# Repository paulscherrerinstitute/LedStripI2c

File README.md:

# Bar-Graph Display Project

Display current pulse-ID on a LED-bar.
The LEDs are driven by PCA9955 LED controllers
and remote-controlled by I2C over a fiber
connection.

 - [kicad/](kicad/)

   Kicad design files; [schematics](kicad/ledstrip-sch.pdf) and pcb.

 - [hdl/](hdl/)

   vhdl code for driving the device from a FPGA
   ([documentation](hdl/README.md)).

 - [python/](python/)

   python scripts to drive the device from the USB/I2C
   adapter (for testing).

 - [PulseidExtractor/](PulseidExtractor/)

   submodule required to extract the pulse-id from an EVR320
   stream.

The LED device's I2C bus is accessible by three methods:

 - optical (light <-> logic 'low' on I2C bus) 
 - PMOD connector (1.5-3.3 V via i2c-transceiver) for
   connection, e.g., to a Zynq board.
 - USB-I2c bridge from host.

Note that in all use-cases power (5V, 350mA max.) must be
provided at the USB port (from host or USB wall-wart).

A mini-USB connector was deemed mechanically more stable than
micro-USB. USB-C would be an alternative.

Till Straumann, 10/2020.

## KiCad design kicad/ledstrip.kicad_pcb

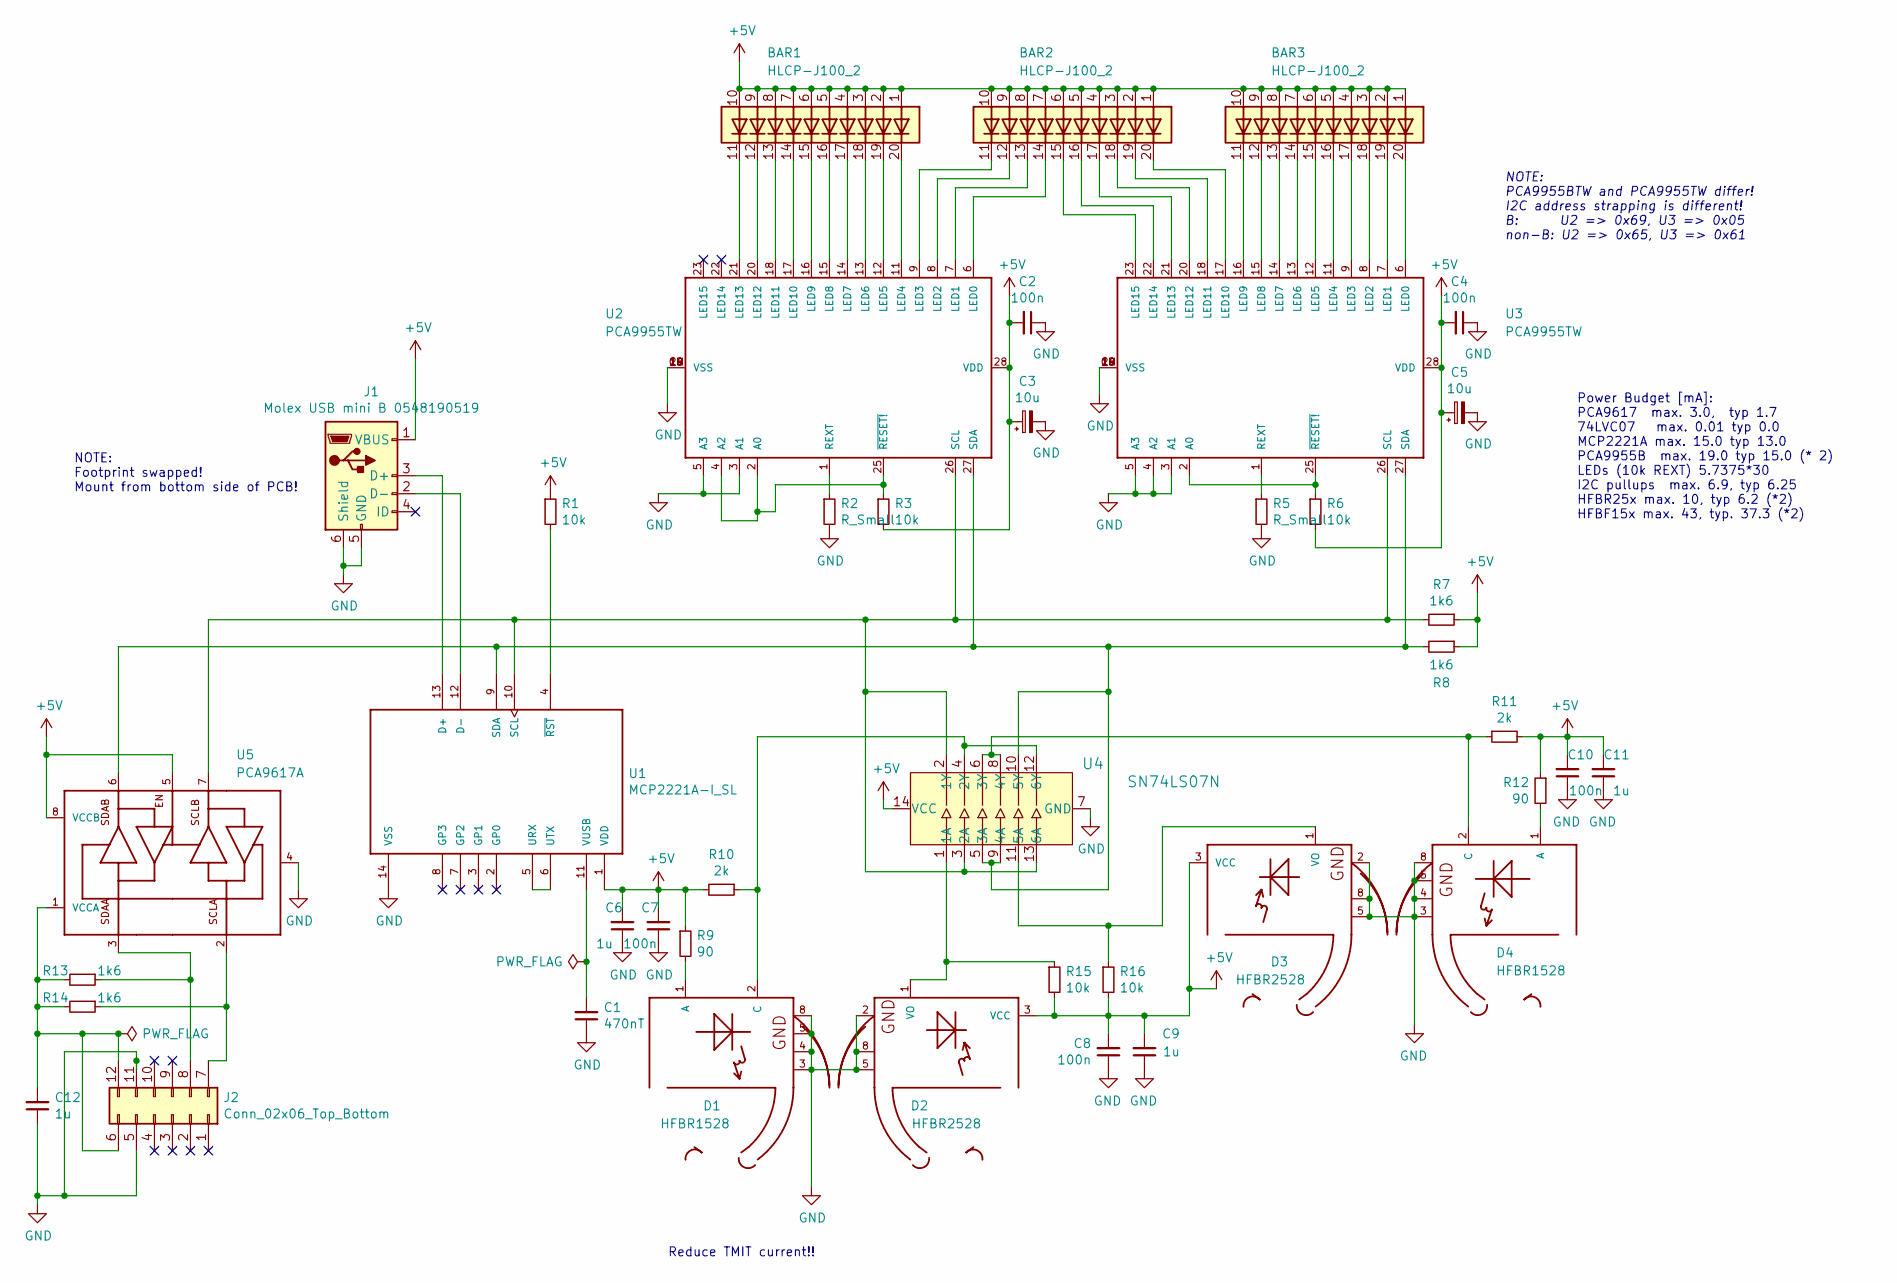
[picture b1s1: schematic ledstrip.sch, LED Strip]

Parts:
BAR1, BAR2, BAR3: HLCP-J100_2; HLCP-J100
C1: 470nT; C_0805_2012Metric
C2, C4, C7, C8, C10: 100n; C_0603_1608Metric
C3, C5: 10u; CP_EIA-3216-10_Kemet-I
C6, C9, C11, C12: 1u; C_0805_2012Metric
D1, D4: HFBR1528; HFBR25XX
D2, D3: HFBR2528; HFBR25XX
J1: Molex USB mini B 0548190519; USB_Mini_B_Female_548190519
J2: Conn_02x06_Top_Bottom; PMOD_PinHeader_2x06_P2.54mm_Horizontal
R1, R3, R6, R15, R16: 10k; R_0603_1608Metric
R2, R5: R_Small; R_0603_1608Metric
R7, R8, R13, R14: 1k6; R_0603_1608Metric
R9, R12: 90; R_1206_3216Metric
R10, R11: 2k; R_0603_1608Metric
U1: MCP2221A-I_SL; SOIC127P600X175-14N
U2, U3: PCA9955TW; SOT1172-2
U4: SN74LS07N; SOIC-14_3.9x8.7mm_P1.27mm; MPN SN74LS07N; Digi-Key_PN 296-1629-5-ND
U5: PCA9617A; TSSOP-8_W3mm

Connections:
+5V: BAR1.1 (A), BAR1.2 (A), BAR1.3 (A), BAR1.4 (A), BAR1.5 (A), BAR1.6 (A), BAR1.7 (A), BAR1.8 (A), BAR1.9 (A), BAR1.10 (A), BAR2.1 (A), BAR2.2 (A), BAR2.3 (A), BAR2.4 (A), BAR2.5 (A), BAR2.6 (A), BAR2.7 (A), BAR2.8 (A), BAR2.9 (A), BAR2.10 (A), BAR3.1 (A), BAR3.2 (A), BAR3.3 (A), BAR3.4 (A), BAR3.5 (A), BAR3.6 (A), BAR3.7 (A), BAR3.8 (A), BAR3.9 (A), BAR3.10 (A), C2.2, C3.1, C4.2, C5.1, C6.2, C7.2, C8.2, C9.2, C10.2, C11.2, D2.3 (VCC), D3.3 (VCC), J1.1 (VBUS), R1.1, R3.2, R6.2, R7.1, R8.1, R9.1, R10.2, R11.2, R12.1, R15.2, R16.2, U1.1 (VDD), U2.28 (VDD), U3.28 (VDD), U4.14 (VCC), U5.5, U5.8 (VCCB)
GND: C1.1, C2.1, C3.2, C4.1, C5.2, C6.1, C7.1, C8.1, C9.1, C10.1, C11.1, C12.1, D1.3, D1.4, D1.5, D1.8, D2.2, D2.5, D2.8, D3.2, D3.5, D3.8, D4.3, D4.4, D4.5, D4.8, J1.5 (GND), J1.6 (Shield), J2.5, J2.11, R2.2, R5.2, U1.14 (VSS), U2.3 (A1), U2.5 (A3), U2.10 (VSS), U2.19 (VSS), U2.24 (VSS), U2.CM (VSS), U3.3 (A1), U3.4 (A2), U3.5 (A3), U3.10 (VSS), U3.19 (VSS), U3.24 (VSS), U3.CM (VSS), U4.7 (GND), U5.4
unnamed: BAR1.11 (K), U2.21 (LED13)
unnamed: BAR1.12 (K), U2.20 (LED12)
unnamed: BAR1.13 (K), U2.18 (LED11)
unnamed: BAR1.14 (K), U2.17 (LED10)
unnamed: BAR1.15 (K), U2.16 (LED9)
unnamed: BAR1.16 (K), U2.15 (LED8)
unnamed: BAR1.17 (K), U2.14 (LED7)
unnamed: BAR1.18 (K), U2.13 (LED6)
unnamed: BAR1.19 (K), U2.12 (LED5)
unnamed: BAR1.20 (K), U2.11 (LED4)
unnamed: BAR2.11 (K), U2.9 (LED3)
unnamed: BAR2.12 (K), U2.8 (LED2)
unnamed: BAR2.13 (K), U2.7 (LED1)
unnamed: BAR2.14 (K), U2.6 (LED0)
unnamed: BAR2.15 (K), U3.23 (LED15)
unnamed: BAR2.16 (K), U3.22 (LED14)
unnamed: BAR2.17 (K), U3.21 (LED13)
unnamed: BAR2.18 (K), U3.20 (LED12)
unnamed: BAR2.19 (K), U3.18 (LED11)
unnamed: BAR2.20 (K), U3.17 (LED10)
unnamed: BAR3.11 (K), U3.16 (LED9)
unnamed: BAR3.12 (K), U3.15 (LED8)
unnamed: BAR3.13 (K), U3.14 (LED7)
unnamed: BAR3.14 (K), U3.13 (LED6)
unnamed: BAR3.15 (K), U3.12 (LED5)
unnamed: BAR3.16 (K), U3.11 (LED4)
unnamed: BAR3.17 (K), U3.9 (LED3)
unnamed: BAR3.18 (K), U3.8 (LED2)
unnamed: BAR3.19 (K), U3.7 (LED1)
unnamed: BAR3.20 (K), U3.6 (LED0)
unnamed: C1.2, U1.11 (VUSB)
unnamed: C12.2, J2.6, J2.12, R13.2, R14.2, U5.1 (VCCA)
unnamed: D1.1 (A), R9.2
unnamed: D1.2 (C), R10.1, U4.4 (2Y), U4.12 (6Y)
unnamed: D2.1 (VO), R15.1, U4.1 (1A)
unnamed: D3.1 (VO), R16.1, U4.11 (5A)
unnamed: D4.1 (A), R12.2
unnamed: D4.2 (C), R11.1, U4.6 (3Y), U4.8 (4Y)
unnamed: J1.2 (D-), U1.12 (D-)
unnamed: J1.3 (D+), U1.13 (D+)
unnamed: J2.7, R14.1, U5.2
unnamed: J2.8, R13.1, U5.3
unnamed: R1.2, U1.4 (~RST~)
unnamed: R2.1, U2.1 (REXT)
unnamed: R3.1, U2.2 (A0), U2.4 (A2), U2.25 (~RESET!~)
unnamed: R5.1, U3.1 (REXT)
unnamed: R6.1, U3.2 (A0), U3.25 (~RESET!~)
unnamed: R7.2, U1.10 (SCL), U2.26 (SCL), U3.26 (SCL), U4.2 (1Y), U4.3 (2A), U4.13 (6A), U5.7
unnamed: R8.2, U1.9 (SDA), U2.27 (SDA), U3.27 (SDA), U4.5 (3A), U4.9 (4A), U4.10 (5Y), U5.6
unnamed: U1.5 (URX), U1.6 (UTX)

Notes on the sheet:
Reduce TMIT current!!
Power Budget [mA]: PCA9617 max. 3.0, typ 1.7 74LVC07 max. 0.01 typ 0.0 MCP2221A max. 15.0 typ 13.0 PCA9955B max. 19.0 typ 15.0 (* 2) LEDs (10k REXT) 5.7375*30 I2C pullups max. 6.9, typ 6.25 HFBR25x max. 10, typ 6.2 (*2) HFBF15x max. 43, typ. 37.3 (*2)
NOTE: PCA9955BTW and PCA9955TW differ! I2C address strapping is different! B: U2 => 0x69, U3 => 0x05 non-B: U2 => 0x65, U3 => 0x61
NOTE: Footprint swapped! Mount from bottom side of PCB!

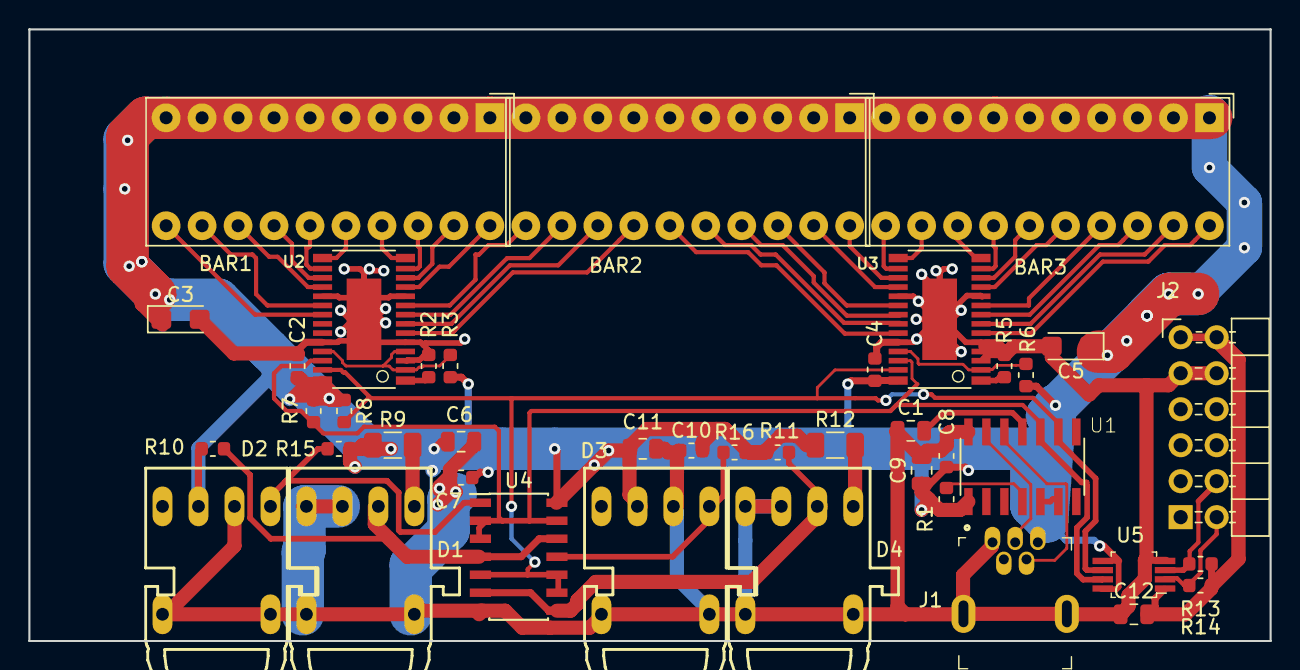
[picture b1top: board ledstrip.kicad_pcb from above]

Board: 2 copper layers, 87.6 x 43.2 mm, 41 parts (0 on the bottom side), 52 nets.

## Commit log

2020-10-08 Added new...
2020-10-08 First python implementation
2020-10-08 mcp2221_i2c.py: added more functionality
2020-10-08 renamed mcp2221_i2c.py -> Mcp2221I2c,py; added LedStrip.py
2020-10-08 changed some sleep times in test routine
2020-10-08 LedStrip.py: setPwmIref() accepts arrays/collections
2020-10-14 Mcp2221I2c.py: Support writing chip settings to flash
2020-10-15 Changed 'drain'; support restart+write; ensure device is drained before sending new read/write commands
2020-10-20 initial import from PON
2020-10-20 ioxos_mpc_master_i2c_ctl.vhd: convert to numeric_std; don't set ila signals if ila is disabled
    setting ila signals caused warnings about to_unsigned range errors
    (target slv too short).
2020-10-20 ila_dummy.vhd: added (for ghdl)
2020-10-20 i2ctb.vhd: added test bed
2020-10-20 i2ctb.vhd: added several helper procedures
2020-10-21 Added PulseID Extractor module.
    Extract pulse ID from EVR stream.
2020-10-21 Added MpcI2cSequencer
2020-10-21 made initial FDR value a generic
2020-10-21 Added LedStripController.vhd
2020-10-21 - added i2cRegSlaveWrap.vhd for testing
2020-10-21 ioxos_mpc_master_i2c_ctl.vhd: support small prescaler dividers
    If FDR(7) is set then we use FDR(6 downto 0) literally.
    Also: allow for read-only FDR (save a bit of logic) via generic
2020-10-21 bugfixes
2020-10-21 Added LedStripMmioWrapper.vhd
2020-10-21 Moved test code to 'tb/'
2020-10-21 more test code to 'tb/'
2020-10-21 made strobe rate run-time modifiable
2020-10-21 added debugging signals
2020-10-21 MmioWrapper: use word address!
2020-10-21 more debugging signals
2020-10-21 fixed bit-length error in debugging signal assignment;
2020-10-21 another vector-length fix
2020-10-21 fixed wrong range in debug state vector
2020-10-22 Must handle arbitration loss to avoid hangs
2020-10-22 MpcI2cSequencer.vhd: added missing definition for ST_MAL bit
2020-10-22 MpcI2cSequencer.vhd: added missing ';'
2020-10-22 Made gray-code enablement a run-time option
2020-10-22 Run-time support for FDR fixes, updated tests
2020-10-22 LedStripMmioWrapper.vhd: vivado packager didn't grok to_unsigned in generic default assignment
2020-10-22 Fixed some errors reported by vivado (passed ghdl, though)
2020-10-22 added debouncer to git
2020-10-22 LedStripMmioWrapper.vhd: removed unused signal that was set but not declared
2020-10-22 psi-file-list.tcl: added
2020-10-22 psi-file-list.tcl: cosmetics
2020-10-22 LedStripMmioWrapper.vhd: needed another work-around to make the vivado packager happy :-(
    It cannot understand BLAH := "1" & "1100"; (concatenation)!
2020-10-22 LedStripController.vhd: added comment
2020-10-23 LedStripMmioWrapper.vhd: enable gray-code by default in control-register
2020-10-26 PulseidExtractor.vhd: added synchronizer for strobe signal as well as async output clock
2020-10-26 PulseIdExtractor.vhd: added trigger feature
2020-10-26 moved hdl into hdl/ subdir
2020-10-26 added makefile for testbed
2020-10-26 Moved python and C into separate subdirs
2020-10-26 Added README.md
2020-10-26 Added kicad design files to git
2020-10-26 Added kicad/README.errata file
2020-10-27 updated README.errata
2020-10-27 MpcI2cSequencer: added support for read operations
2020-10-27 MpcI2cSequencerPkg.vhd: added comments
2020-10-27 updated makefile for test
2020-10-28 LedStripController.vhd: read-back and verify PID data; keep error counters
    Also updated test-beds.
2020-10-28 MpcI2cSequencerPkg.vhd: added 'getFDRVal()' to compute FDR value
    Compute from bus- and scl-frequencies running through the table
    if necessary.
2020-10-28 Updated MMIO wrapper to include error counter register readbacks
2020-10-28 LedStripMmioWrapper.vhd: vivado IP packager doesn't support real generics
    Work-around by using integers...
2020-10-28 More tweaks to make vivado IP packager happy (^&(*&^(%%%)
2020-10-28 LedStripMmioWrapper.vhd: added support for marker LEDs
2020-10-28 Added wrapper for tosca/tcsr; rewrote mmio wrapper to use the former
2020-10-28 LedStripTcsrWrapper.vhd: must gray-encode upstream of setting marker LEDs
2020-10-28 PulseidExtractor.vhd: use registered pulseid to help timing (when crossing to user clk)
2020-10-28 LedStripTcsrWrapper.vhd: added mux for selecting an update-trigger.
2020-10-28 LedStripTcsrWrapper.vhd: synchronize mux into EVR clock domain.
2020-10-28 LedStripTcsrWrapper.vhd: created block (help naming stuff in ucf files)
2020-10-28 psi-file-list.tcl: added Tcsr wrapper
2020-10-28 LedStripTcsrWrapper.vhd: made default SCL freq. a generic
2020-10-29 Added README.md for firmware
2020-10-29 updated documentation
2020-10-29 Redrew HFBR component graphics (had rendered badly in PDF)
2020-10-29 ledstrip.sch: added some comments
2020-10-29 added PDF of schematics
2020-10-29 README.md: cosmetics
2020-10-29 README.md: more cosmetics
2020-10-29 hdl/README.md: clarification
2020-10-29 Added watchdog for missing pulseID updates
2020-10-29 Revert watchdog addition; LedStripController strobe may be decimated
2020-10-29 PulseIdExtractor: use EvrStreamType
2020-10-29 Added synchronization checks and watchdog to PulseIdExtractor
    Watchdog checks that we get a regular pulse ID stream
2020-10-29 PulseIdExtractor: moved error counters into output clock domain
2020-10-29 PulseIdExtractor: run watchdog in output clock domain
    This way we only need one know frequency for computing
    cycle counts (in parent module).
2020-10-29 LedStripTcsrWrapper.vhd: added synError and watchdog error counters
2020-10-29 Added counter for delivered (decimated) pulse IDs
2020-10-29 Added counter to verify that pulse-ids are sequential
2020-10-29 LedStripMmioWrapper.vhd: adapted tcsrADD width (which has changed)
2020-10-29 LedStripMmioWrapper.vhd: must rearrange local regs
2020-10-29 Added Version Register
2020-10-29 LedStripTcsrWrapper.vhd: added missing ';'
2020-10-29 Updated hdl/README.md adding info about generics, constraints etc.
2020-10-29 updated README (constraints section)
2020-10-29 README.md: fixed indentation
2020-11-09 Renamed LedStripTcsrWrapperPkg -> Evr320StreamPkg
    The definitions in this package have nothing to do with the LedStrip...
2020-11-09 Fixed PulseIDExtractor (seq errors, pidCount)
    Must check seq errors independently of trigger (decimated
    IDs are not sequential).
    For pidCount count the number of watchdog strobes; this is more
    valuable in case you want to debug trigger problems...
2020-11-09 Added PulseidAtomic.vhd, PulseidAtomicTmem.vhd
2020-11-09 Added LedStripTmemWrapper.vhd (moved some declarations to LedStripWrapperPkg)
2020-11-09 renamed BUSY, PIPE outputs
2020-11-10 PulseidExtractor.vhd: bugfixes
    - must check sequence of pulse-ids on every update, not just when
    trigger is set. If the trigger is used to decimate IDs then the
    previous method would flag sequence errors when there were none.
    - increment pulse ID (statistics) counter on every arriving new
    PID. This is more useful than counting triggers (which is equivalent
    with the PID itself). Allows for diagnosing problems with the
2020-11-10 LedStripTmemWrapper.vhd: FIX: write loop accessed 5 byte lanes instead of 4
2020-11-10 PulseidAtomic.vhd, PulseidAtomicTmem.vhd: used package was renamed to Evr320StreamPkg
2020-11-10 PulseidAtomicTmem.vhd: Added counter-reset bit to control reg.
2020-11-10 psi-file-list.tcl: updated/fixed
2020-11-10 Moved PulseidExtractor to separate git submodule
2020-11-10 PulseidExtractor was migrated to an external module (which we reference as a submodule).
2021-02-18 LedStripTmemWrapper.vhd: BUGFIX: must check IF_ENA when writing!
